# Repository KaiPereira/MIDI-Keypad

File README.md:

# Design your own MIDI keypad

Ever wanted to cook up and mix your own beats while simultaneously learning PCB design? Well look no further because your [local Kai](https://github.com/KaiPereira) is about to show you how to make your own custom MIDI keypad completely from scratch.

Now this is YOUR MIDI device, so please use this tutorial as a loose guide and come up with your own custom layout and features to make it awesome; go crazy!! 

We'll be using these core components, and you should use any amount and combination of them for your design:
- EC11 Rotary Encoders
- SK6812 MINI-E Neopixels
- Bourns Slide Potentiometers
- Kailh Choc Low-Profile Switches
- Any other components you want, but I won't walk you through wiring them

And then your actual MIDI keys will use capacitive touch which just uses exposed copper on the PCB which uses the electrical field from your body to detect presses!

## Setting up KiCad

We'll be using KiCad (which you'll need to install) for your PCB design, if you're not familiar with it, don't worry, because this tutorial is totally beginner friendly!

KiCad has tens of thousands of parts for you to use in the editor, but they're still missing a couple which we'll need to install. So [head on over to the library](https://github.com/KaiPereira/Hackclub-KiCad-Libraries) I've made, which includes instructions on downloading these parts we're missing!

Once you've installed the library, we can get right into creating your schematic! The schematic shows how the components on your PCB will be wired, but it doesn't physically place them on your PCB, which we do in another step!

So first launch KiCad and then go "file -> new project" and use the default template and call it whatever you want! Double click on this .kicad_sch file and it'll open up the schematic editor:

There's a couple important keybinds to keep in mind when designing PCBs:
- "a" will open up the symbol library where you can search for symbols/components
- "w" will allow you to create a wire which you'll connect symbols with
- "l" will place a net label down, which essentially says this thing connects to this, similar to a wire, but looks more clean in larger schematics
- "e" will allow you to modify the details of symbols
- "q" will add a no-connect flag (which looks like a blue X) which essentially says nothing wires to this pin which makes your schematic look cleaner and you'll notice me use it a little bit

## Building Your Schematic

### The Microcontroller!

The first thing we're going to add into our schematic, is our MCU or microcontroller. You have 2 options for microcontrollers:
- The [XIAO ESP32-S3](https://wiki.seeedstudio.com/xiao_esp32s3_getting_started/), less IO, cheaper, smaller
- The [Waveshare ESP32-S3-Zero](https://docs.waveshare.com/ESP32-S3-Zero), more IO, more expensive and larger

Add in your chosen MCU in the symbol library using that "a" keybind we talked about:

Next, we're going to wire up our power pins, because we'll be using these quite a lot in other spots on our schematic. These are called power labels and you can just find them in the symbol library:

Your voltage labels should always point upwards, and your ground labels should always point downwards because once you make more complicated PCBs, it makes it really easy to read your schematics. You should also never have overlapping wires or text in your schematics, that again makes it hard to read!

### Other Components

Next you have the option of adding your own components for your own customizable MIDI keypad! I'll show you how to wire a couple of these components, and please make your own combination of them, you have total creative freedom:

#### Capacitive Touch Keys

On our MIDI keypad, we can add capacitive touch keys. These use the electrical fields generated by your body to detect if they're being touched and look awesome on your PCB!

To wire it, we'll use pin headers to represent each of our keys, so a 01x07 pin headers for 7 keys for example:

All the GPIOs except RX/TX on our Waveshare ESP32-S3-Zero can be used for capacitive touch, but only a couple on the XIAO ESP32-S3 can be used so [check the pinout](https://wiki.seeedstudio.com/xiao_esp32s3_getting_started/) for that MCU.

We'll use net labels to wire these together, so tap "l" and add them in:

Always add nice wires underneath your net labels so they're easy to read.

#### Low-Profile Switches

If you want to make part of your MIDI keypad have nice keyboard switches, we can easily add some in! You can just wire the switches to ground and if you want even more switches, you should look into wiring them [as a matrix](https://www.dairequinlan.com/2020/12/the-keyboard-part-2-the-matrix/) instead which needs some diodes but lets you have TONS of keys by using up less GPIOs. 

*You would want to get some nice keycaps for your switches.*

*Note that RX and TX on the Waveshare MCU can be reprogrammed in your firmware to just be normal GPIO pins so they're fine to use for your switches and any other component except the capacitive touch keys which need special IOs.*

#### EC11 Rotary Encoder 

The EC11 rotary encoder has both an encoder and a switch if you want to wire it so you can also press it down. I'm only using the encoder part because I don't have much IO left and want to add some more stuff.

It's pretty easy to wire, it's just 2 IO pins for each direction of the pin and then a ground connection, and you can wire the switch looking part of the symbol like a normal switch or part of a matrix.

#### Bourns Slide Potentiometer

The Bourns slide potentiometer is a large slider you can add to your PCB. You can just wire pins 1 and 3 to ground and +3V3 respectively, and then wire pin 2 to an analog IO to detect its state and then the mounting pins can just be grounded. 

Adding the slide potentiometer will probably increase the cost of your project a fair amount because you can't source it on Aliexpress, but you might be able to find an alternative or something.

*Your slider needs to be wired up to an analog capable pin on your MCU, so check the pinouts  on your MCU again and make sure the pin is ADC capable*

You'll want to use the "R_Potentiometer_MountingPin" symbol for this, and I've renamed my symbols here to make it more obvious what they're actually being used for.

#### SK6812MINI-E Neopixels

The SK6812MINI-E neopixels let you add RGB lighting to your keypad. Just wire up the power and ground pins, and then you can chain them together like so. When programming these neopixels, you'll be able to program them as the chain and can control each individually with just that singular pin. 

*These mount on the backside of your PCB and have a hole through the PCB so they can shine through the board*

### Assigning Footprints

Now that we've finished our schematic, which shows the electrical connections between components, we need to assign the footprints which are the actual physical representations of the component on your PCB.

To assign the footprints, tap the "assign footprints" button in the top toolbar. Some of your symbols might already have their footprints assigned, but we still need to assign the ones we're missing:
- The switches (SW_PUSH) can just be assigned the "Kailh Choc Low-Profile Switches" which is inside of the footprint library you downloaded at the start of this tutorial
- The rotary encoder can be assigned the vertical EC11 footprint
- The slide potentiometer can be assigned any size Bourn slide potentiometer you want
- The SK6812MINI-E is auto-assigned
- Leave your capacitive keys footprint empty for now, we'll be making a custom footprint for this!

This is what my footprints look like after:

## Designing the Actual PCB

Now that you've assigned your footprints, we can start designing the actual PCB. Import all your parts by first tapping "Switch to PCB" in the top toolbar of the **schematic editor**, and then tap "Update PCB from Schematic" in the PCB editor and then update your PCB:

### Creating Our Capacitive Keys

Now the only footprint we're missing is our capacitive keys! Open the KiCad footprint editor (there's a button in the top toolbar of the PCB editor for it), and then go "file -> new footprint":

Set your grid to 1.0mm in the top toolbar, so it's easier to make precise geometry for your footprint. I would suggest changing your grid constantly to keep accurate and symmetrical geometry, don't make an ugly footprint.

Now this is where you have a lot of freedom. You can make your capacitive keys any shape you want, squares, circles, rectangles, polygons, even drawings if you so wish (you can search up how to do so). I'm gonna make mine look like piano keys for the sake of simplicity, but go crazy.

So go to your right hand toolbar, and add a pad:

Tap your pad, and then tap "e" to bring up all of its properties. This is where you can customize your pads to look however you want but you need to do 2 things first:
- Set your pad type to SMD which removes that hole in the pad
- Uncheck the F.Paste layer, which is if you get automated PCB assembly or buy a stencil, which prevents the pads from having solder applied to them

Then set the pad number to 1 for the first pad, this just maps pin 1 on the symbol, to this pad of the footprint, so if you have 7 keys we'll be adding 7 pads labelled 1 through 7.

Then, you just manipulate the sizes of the pad and move them around to create your footprint. I've gone ahead and built a key footprint by using a bunch of squares and vectors, but just make your capacitive keys any shape you want, just make sure the spacing between copper is at least 0.2mm!

I'd also suggest iterating over your footprint if it doesn't fit your PCB nicely once you add it in. 

You should also add a courtyard, which just prevents you from putting components physically on-top of your footprint, but if you're careful, you don't necessarily need it, but I'd highly suggest having one: You can add one by tapping the F.Courtyard layer and then drawing something onto it.

*The courtyard is the pink boundary around the footprint*

Next, you'll need to create your own footprint library to save this to because the default one is read only and you don't have write permissions for it.

So go "file -> new library" and just call it whatever. I call mine "Kai's Library" and once you save it (I would also name it something like "Capacitive Keys"), you'll notice it show up in your library on the left hand side if you search for it. 

Then go back to your schematic editor and assign the footprint:

Go back to the PCB editor, and then import it in using the update PCB from schematic:

### Designing the PCB 

Now the first thing you want to do on your PCB is nicely lay out your components on the PCB, into the general shape you want it to look like. I'd suggest making it under 100x100mm because it makes the PCB cheaper to order, but you have complete creative freedom. Just make sure that if you have neopixels, to flip what side they are on your PCB (using "f") so that they're reverse mounted and shine through the PCB:

PCB design is a constantly iterative design process, so when laying out your board, routing it, etc, feel free to move stuff anytime. I would take advantage of the different grids you can use in KiCad to nicely align stuff, this board is mostly made with 1mm, 0.5mm and 0.25mm grids.

Now the first thing I'm actually going to do, is modify the net labels on my schematic so that it's easier to route the boards, and to reduce the amount of those straight blue lines/unrouted traces that we call ratsnest, intersecting:

I'm quite experienced at routing PCBs so I'm pretty good at just looking at my board and doing this, but feel free to do it iteratively if you ever have weird crossing traces that aren't the prettiest. 

Next, we'll add in our PCB board edge. Tap the edge.cuts layer on the right hand side, and then tap on the square or whatever shape you want your PCB. I'd suggest putting the USB-C receptacle of your MCU over the board edge so it's easy to plug in, and it'll be handy when you make the case for your keyboard. I'd also suggest rounding your edges, by tapping the outline, tapping "e" and then modifying the corner radius value so your board looks prettier:

Now we get to actually route the traces for our PCB! You can tap the route button on the right hand toolbar, or you can just tap "x" to start routing. I'm not going to walk you through this, but there's a couple things you should keep in mind:
- Try to avoid 90 degree traces, they're ugly and they become a bigger concern when doing high speed design (we're NOT doing any though) so it's not great to get in the habit of doing it. They are slightly important for the capacitive touch keys because of the nature of those signals, but it's not a major concern
- Don't be afraid to re-route/delete and re-do traces if it's difficult to get somewhere or ugly to do so, it's very common in PCB design. You can tap a trace, and then tap "u" to highlight and delete the entire thing at once.
- Keep the capacitive touch traces away from the other traces because they're sensitive to the noise induced from other signals
- If you add a ground plane to your PCB, don't fill near the capacitive touch keys, or at least pay attention to it, because it'll dampen the signals (if you don't know what I'm talking about, don't worry about it)

You get 2 layers to route your PCB on, the F.Cu and B.Cu layer. You can transition between these layers by placing down a via (which is essentially a tiny plated hole on your PCB) while routing on one of them, so while routing, you can just tap "v" and it'll add a via to the end of your trace, and once you place it down, you'll transition to the other layer.

You'll want to route all of your capacitive touch keys first, and try to minimize their length, and just pay attention to them. I'd suggest routing those traces on the front layer, and then routing all the other traces on the back layer. I'm experienced at routing PCBs so don't worry if your boards are a bit uglier:

I'm a bit of a perfectionist, so this is what my final board routing looks like:

### PCB Art and Finishing Touches!

Next, it is an absolute necessity to make our PCB look beautiful by adding art. We do this by moving to the silkscreen layer! F.Silkscreen is the front art, and B.Silkscreen is the back art.

The KiCad project manager window has an image converter which is really useful for converting your images to silkscreen! 

Next, we need to verify that our PCB is ready for manufacturing. We can test this by the "DRC" or design rules check in the top toolbar. So tap the button and check for errors:

All the warnings can be ignored and same with the board edge clearance violations for the *neopixels*. Those are essentially just saying that our pads might be slightly cut off during manufacturing, but that's fine because they're large pads and we'll be hand-soldering them.

So if everything's good, we're onto the final steps!

### 3D Models

Let's add all the 3D models in for our components that don't have one yet. This will make it easier to design the case for our keypad, and will also let us take polished photos of our project. I've added all the 3D models [into the GitHub repository](https://github.com/KaiPereira/MIDI-Keypad/tree/master/PCB/models) for this tutorial, so go ahead and install the ones you need!

If you only have a couple of the component on your board, you should just tap the footprint, tap "e" and then go to the 3D model tab, and then add in the model and move it, for each footprint. But if you have quite a few of that footprint, I would suggest making a copy of the new footprint with the 3D model to your library and then just selecting it for all of that footprint on the board.

And just like that we're done our PCB!

## Fabrication

Now that we're done our PCB, we can actually prepare it for manufacturing.

Before we do anything, make sure that you've run DRC and it's clear of errors that matter, and that your PCB looks fairly polished and nice :D

Next, we're going to install the JLCPCB fabrication toolkit, which is essentially a one-click button that exports all the files we need in order to manufacture our project. The repository nicely goes over how to install it: https://github.com/bennymeg/Fabrication-Toolkit

Once you reload KiCad, you'll see the button pop up at the end of the top toolbar, or you can go "tools -> external plugins -> Fabrication Toolkit" to open it up. And then just simply click generate and it'll make all your production files. If you ever edit your PCB again, make sure to re-generate your fabrication files:

And now if you go into the /production folder it generated, you'll see the:
- Gerbers which is the zip folder and contains all the data for the layers on your PCB
- The bom.csv or "bill of materials" which has all your components in it
- the positions.csv which essentially just says the orientation and placement of those components on your PCB

And there's some other files, but you don't need to worry about those. 

Now we can go over to https://jlcpcb.com/ to order our PCB. Just tap order now, and then upload your gerbers zip file:

For ordering your PCB, I would suggest:
- Changing your shipping to whatever's cheapest to minimize the cost
- If it's cheap, selecting ENIG surface finish so that the exposed copper on your keys doesn't oxidize which can look a bit ugly. If you use ENIG, you should try some exposed copper art on your PCB because it'll look nice and golden! 
- Any other customizations you'd like within budget :D

## Final Steps

You're on the final steps, and you just have to do a couple more things to get your project ready to be shipped!

You need to make a proper BOM or Bill of Materials for your project. This is just a spreadsheet you can export as a .csv with all your parts, where you're going to buy them and their price. I would take a look at [https://codex.hackclub.com/design/part-sourcing/](https://codex.hackclub.com/design/part-sourcing/) on how to do this!

And then you should make a basic firmware file for your project so it's easy to program once you receive your parts and have soldered your PCB. I would suggest using [KMK](https://github.com/KMKfw/kmk_firmware/blob/main/docs/en/Getting_Started.md) for this but you're free to use whatever, just make sure your firmware supports the ESP32-S3.

And then finally, you need to properly ship your project. Take a look at the Codex again to see how to do this [https://codex.hackclub.com/shipping/101/](https://codex.hackclub.com/shipping/101/)!

Once you receive your parts, it's relatively easy to solder them. Just watch a couple videos online on how to do so, and you'll be golden!

Congrats on making your MIDI keypad :D If you liked this tutorial, you'll probably like some of my other work too and should consider [giving me a follow](https://github.com/KaiPereira) on GitHub and [starring the repository](https://github.com/KaiPereira/MIDI-Keypad) for this tutorial.

Happy hacking, and I'd love it if you sent me your finished builds of your MIDI keypads on Slack (@Kai the Jolly Guy) or by email which you can find on [my website](https://kaipereira.com/).

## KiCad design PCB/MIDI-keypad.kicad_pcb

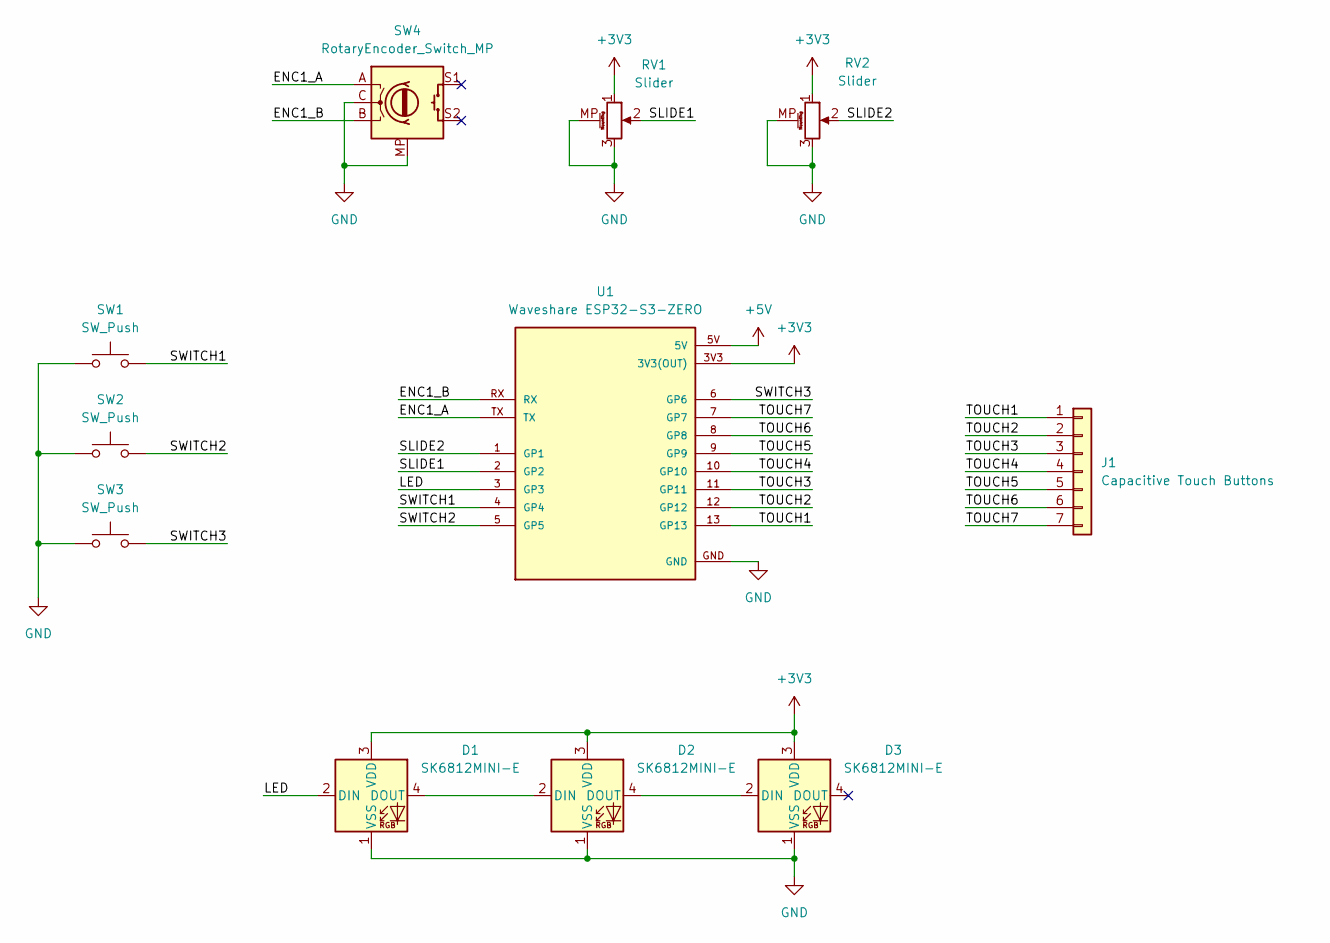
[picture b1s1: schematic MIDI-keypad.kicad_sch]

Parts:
D1, D2, D3: SK6812MINI-E; LED_SK6812MINI-E_3.2x2.8mm_P1.5mm_ReverseMount
J1: Capacitive Touch Buttons; Capacitive Keys
RV1, RV2: Slider; Potentiometer_Bourns_PTA1543_Single_Slide
SW1, SW2, SW3: SW_Push; Kailh Choc Low-Profile Switches
SW4: RotaryEncoder_Switch_MP; RotaryEncoder_Alps_EC11E-Switch_Vertical_H20mm
U1: Waveshare ESP32-S3-ZERO; Waveshare ESP32-S3-Zero; PARTREV NA

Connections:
+3V3: D1.3 (VDD), D2.3 (VDD), D3.3 (VDD), RV1.1, RV2.1, U1.3V3 (3V3(OUT))
+5V: U1.5V
/ENC1_A: SW4.A, U1.TX
/ENC1_B: SW4.B, U1.RX
/LED: D1.2 (DIN), U1.3 (GP3)
/SLIDE1: RV1.2, U1.2 (GP2)
/SLIDE2: RV2.2, U1.1 (GP1)
/SWITCH1: SW1.2, U1.4 (GP4)
/SWITCH2: SW2.2, U1.5 (GP5)
/SWITCH3: SW3.2, U1.6 (GP6)
/TOUCH1: J1.1, U1.13 (GP13)
/TOUCH2: J1.2, U1.12 (GP12)
/TOUCH3: J1.3, U1.11 (GP11)
/TOUCH4: J1.4, U1.10 (GP10)
/TOUCH5: J1.5, U1.9 (GP9)
/TOUCH6: J1.6, U1.8 (GP8)
/TOUCH7: J1.7, U1.7 (GP7)
GND: D1.1 (VSS), D2.1 (VSS), D3.1 (VSS), RV1.3, RV1.MP (MountPin), RV2.3, RV2.MP (MountPin), SW1.1, SW2.1, SW3.1, SW4.C, SW4.MP, U1.GND
unnamed: D1.4 (DOUT), D2.2 (DIN)
unnamed: D2.4 (DOUT), D3.2 (DIN)

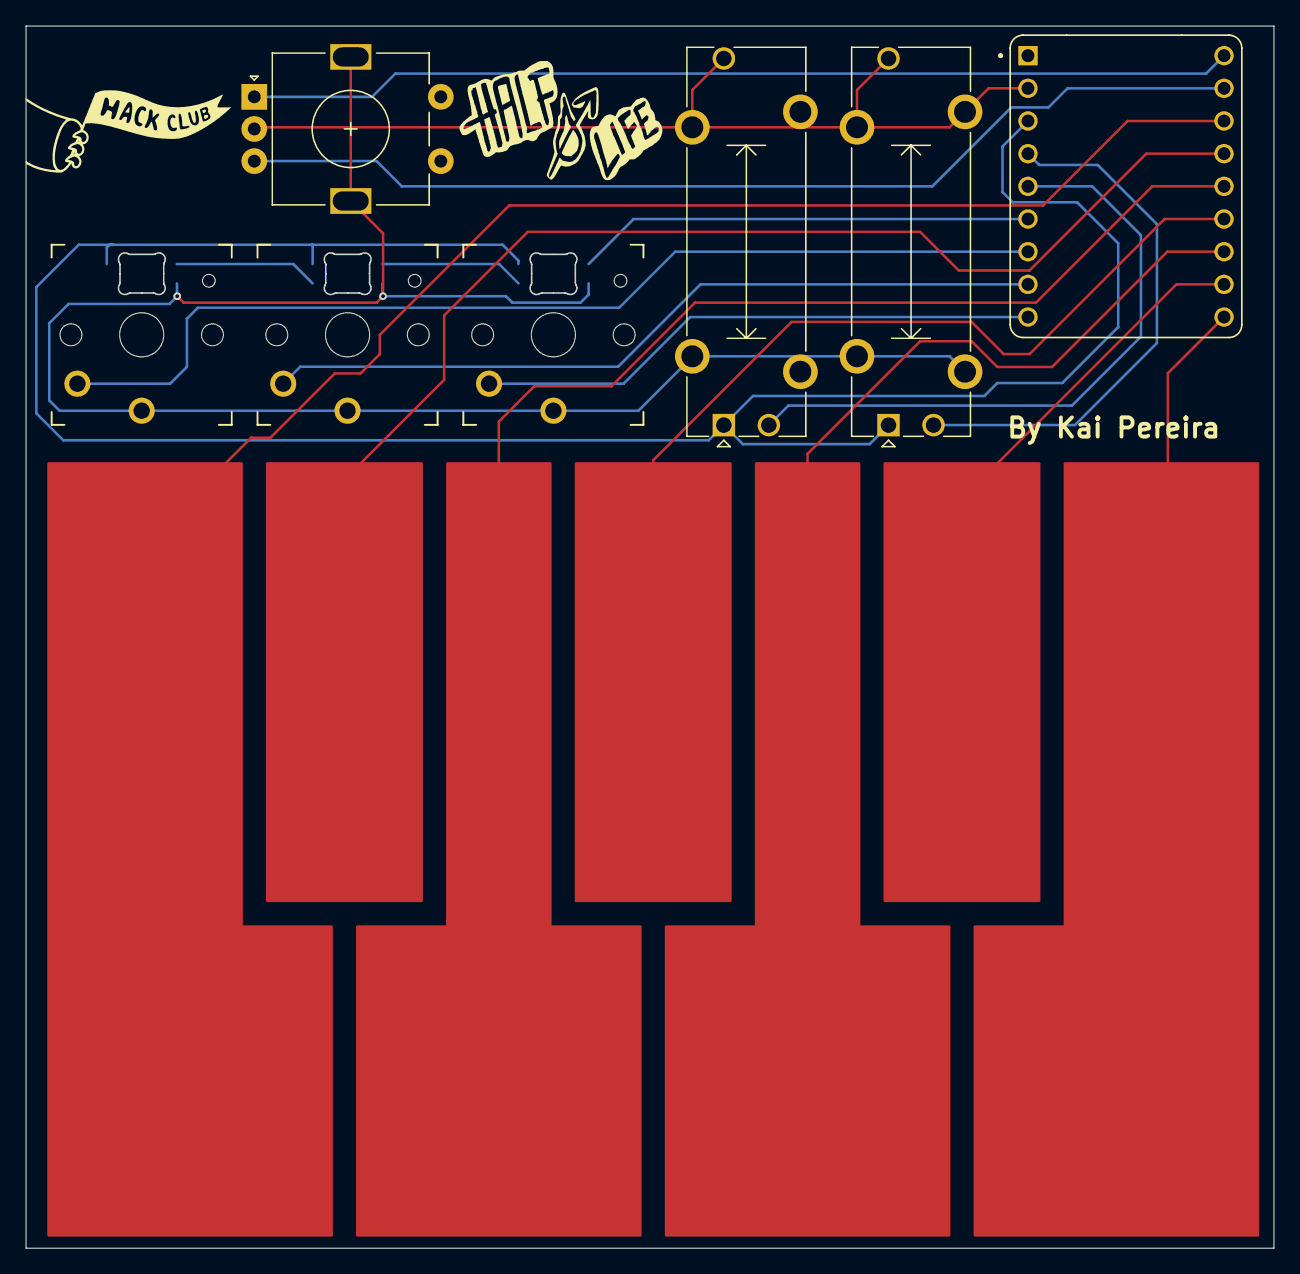
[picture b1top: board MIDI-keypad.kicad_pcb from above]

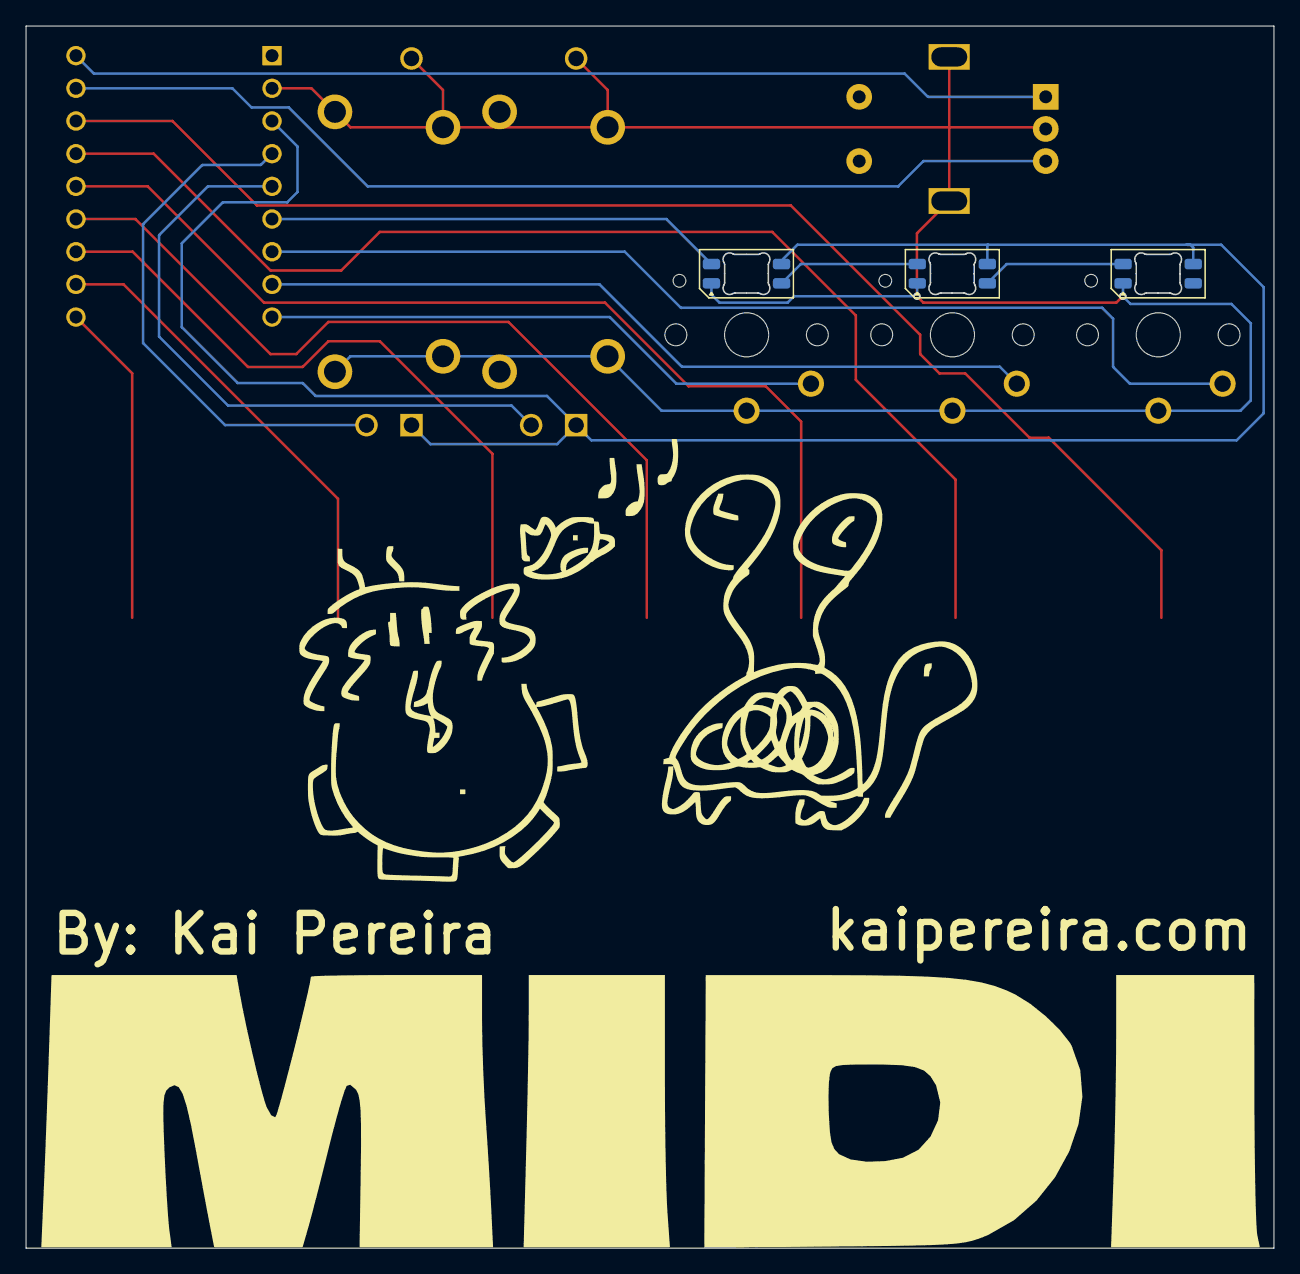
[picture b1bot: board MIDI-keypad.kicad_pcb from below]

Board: 2 copper layers, 97.0 x 95.0 mm, 11 parts (3 on the bottom side), 19 nets.

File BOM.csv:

Designator,Footprint,Quantity,Value,Total Cost,Part
"D1, D2, D3",LED_SK6812MINI-E_3.2x2.8mm_P1.5mm_ReverseMount,3,SK6812MINI-E,$3.36,https://www.aliexpress.us/item/3256807677321116.html?spm=a2g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
J1,Capacitive Keys,1,Capacitive Touch Buttons,,
"RV1, RV2",Potentiometer_Bourns_PTA1543_Single_Slide,2,Slider,$3.16,https://www.digikey.com/en/products/detail/bourns-inc/PTA154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
"SW1, SW2, SW3",Kailh Choc Low-Profile Switches,3,SW_Push,$6.04,https://www.aliexpress.com/item/1005008883418065.html?spm=a2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
SW4,RotaryEncoder_Alps_EC11E-Switch_Vertical_H20mm,1,RotaryEncoder_Switch_MP,$1.44,https://www.aliexpress.us/item/3256807457768762.html?spm=a2g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
U1,Waveshare ESP32-S3-Zero,1,Waveshare ESP32-S3-ZERO,$6.62,https://www.aliexpress.com/item/1005007004089798.html?src=go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
,,,,,
,,,Total Aliexpress:,$19.59,
,,,Total Digikey:,$12.35,
,,,Total JLCPCB: ,$12.29,
,,,Total:,$44.23,
